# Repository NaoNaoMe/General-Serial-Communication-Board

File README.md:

General Serial Communication Board
=========

The General Serial Communication Board is an USB to Serial converter with FTDI Chipset.  
Full/Half-duplex UART, DTR/RTS signals, and 3-position will be adapted microcontroller you may use.  
These features are useful for serial flash programming.  
This board also has opto-isolaters to prevent electrical shock, get rid of Ground Loop track and protect your computer.  

### Some highlights of the General Serial Communication Board:
 1. USB UART Bridge: FTDI FT231X Based on the popular FTDI FT231X converter
 2. UART interface circuit accepts 3.3V and 5.0V.
 3. Electrical isolation between UART interface and USB interface.
 4. All standard serial data rates and up to 3Mega baud.
 5. Full duplex mode and Half duplex mode are selectable(SW4).
 6. Flow control pins are avilable (DTR or RTS, SW1) and (DSR or CTS, SW2)
 7. 3-state user switch(SW3) connected to ftdi is selectable VCC, weak pulldown or GND.
 8. Measures 40mm x 80mm x 20mm

Repository Contents
-------------------
* **/Mechanical** - Mechanical data files (.dxf, .dwg)
* **/Hardware** - All Eagle design files (.brd, .sch)

Description(Pin Interfaces)
-------------------

### CN1(Primarily) Connector Descriptions:
Micro B-type usb connector

### CN2(Secondary) Connector Descriptions:
Barrel Power Jack socket
This socket is connected to VIN pin on CN3 with the main power switch(SW5).  
The power supply must follow microcontroller requirements.

### CN3(Secondary) Pin Descriptions:
This connector is for your target boart.
- **VIN:** UART interface power supply with a voltage range of 2.7 to 5.5VDC.
- **TX:** Full duplex TX signal(CMOS TTL output).
- **TX/RX:** Half duplex signals(Open collector output).
- **RX:** Full duplex RX signal.
- **GND:** GND.
- **I/S:** User switch (Active High signal) and input to DSR or CTS.
- **OUT:** DTR or RTS signal (Active High signal).

License Information
-------------------
The repository is released under [Creative Commons ShareAlike 4.0 International](https://creativecommons.org/licenses/by-sa/4.0/).

Distributed as-is; no warranty is given.

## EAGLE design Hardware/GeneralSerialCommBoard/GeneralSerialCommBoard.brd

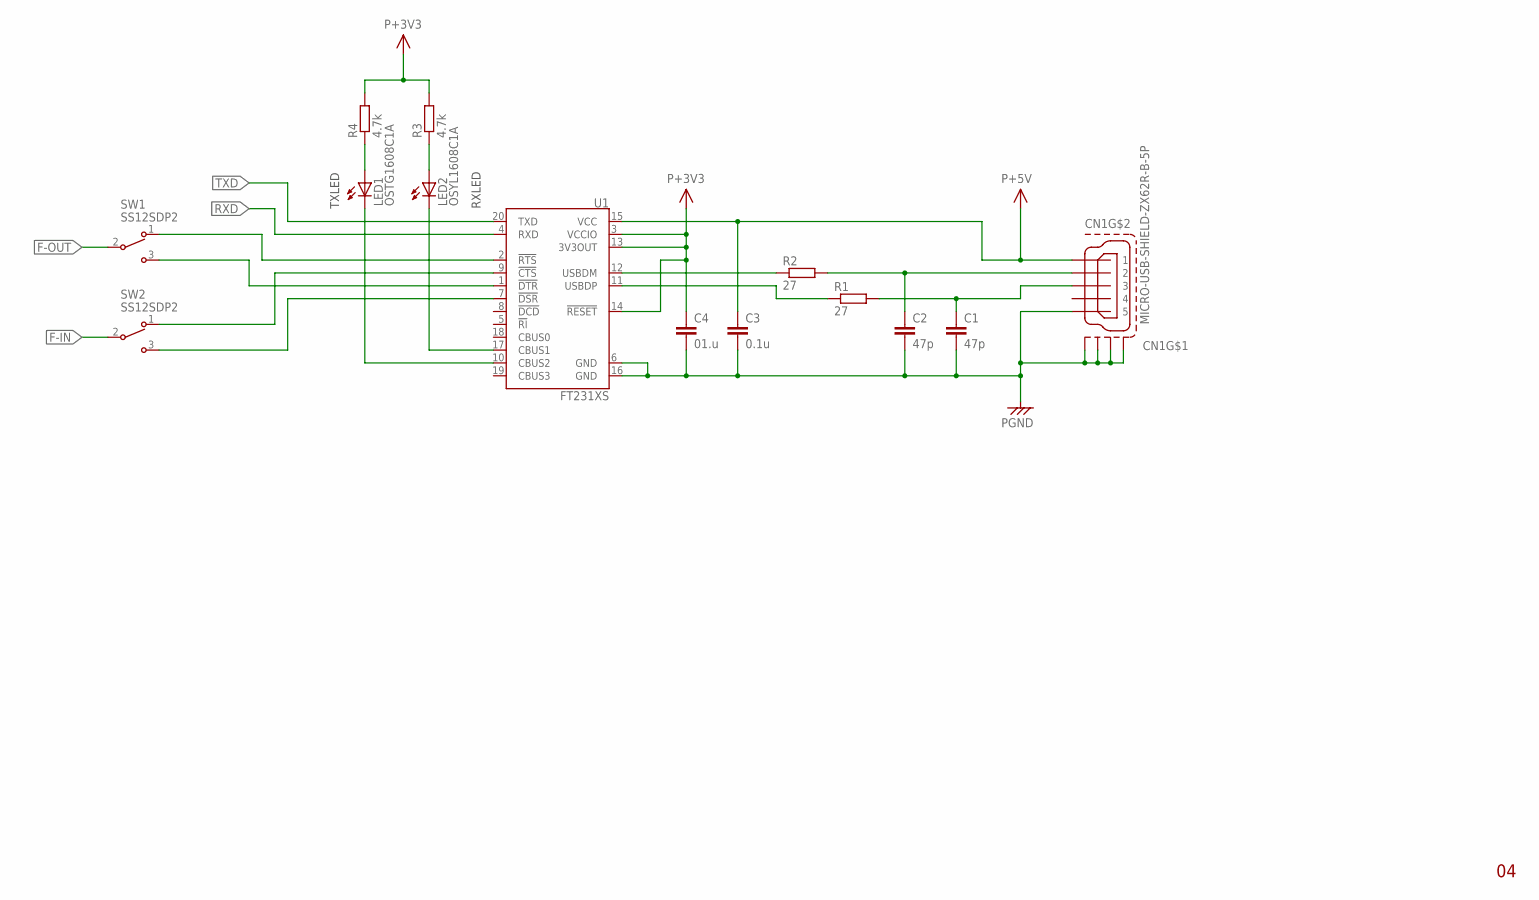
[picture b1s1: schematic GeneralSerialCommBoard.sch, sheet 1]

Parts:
C1, C2: 47p; C0603
C3: 0.1u; C0603
C4: 01.u; C0603
CN1: MICRO-USB-SHIELD-ZX62R-B-5P; ZX62R-B-5P
LED1: OSTG1608C1A; 1608SMD
LED2: OSYL1608C1A; 1608SMD
R1, R2: 27; R0603
R3, R4: 4.7k; R0603
SW1, SW2: SS12SDP2
U1: FT231XS; SSOP20_L

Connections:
CBUS1: LED2.K (C), U1.17 (CBUS1)
CBUS2: LED1.K (C), U1.10 (CBUS2)
CTS: SW2.1 (T1), U1.9 (!CTS)
DSR: SW2.3 (T3), U1.7 (!DSR)
DTR: SW1.3 (T3), U1.1 (!DTR)
F-IN: SW2.2 (COM2); also elsewhere on the board
F-OUT: SW1.2 (COM2); also elsewhere on the board
unnamed: C1.1, CN1.3, R1.2
unnamed: C2.1, CN1.2, R2.2
unnamed: LED2.A, R3.1
unnamed: LED1.A, R4.1
unnamed: R2.1, U1.12 (USBDM)
unnamed: R1.1, U1.11 (USBDP)
P+3V3: C4.1, R3.2, R4.2, U1.3 (VCCIO), U1.13 (3V3OUT), U1.14 (!RESET); also elsewhere on the board
P+5V: C3.1, CN1.1, U1.15 (VCC)
PGND: C1.2, C2.2, C3.2, C4.2, CN1.5, CN1.M1 (S1), CN1.M2 (S2), CN1.M3 (S3), CN1.M4 (S4), U1.6 (GND), U1.16 (GND); also elsewhere on the board
RTS: SW1.1 (T1), U1.2 (!RTS)
RXD: U1.4 (RXD); also elsewhere on the board
TXD: U1.20 (TXD); also elsewhere on the board

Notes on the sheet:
TXLED
RXLED

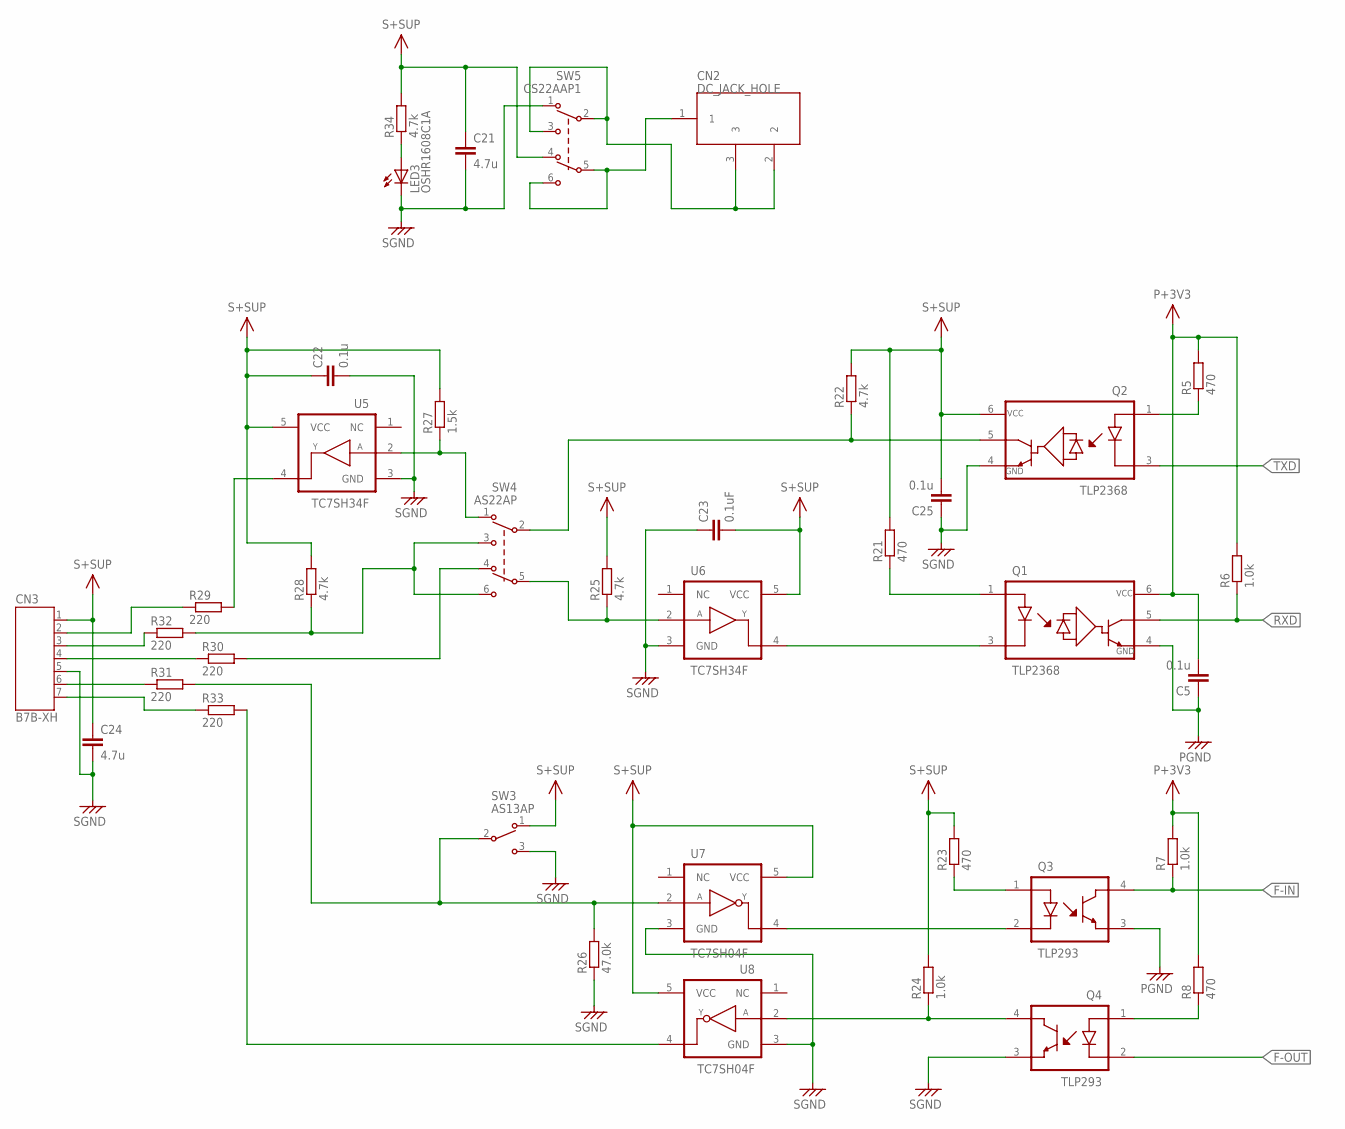
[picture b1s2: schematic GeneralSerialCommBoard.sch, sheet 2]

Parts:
C5, C22, C25: 0.1u; C0603
C21, C24: 4.7u; C1206
C23: 0.1uF; C0603
CN2: DC_JACK_HOLE
CN3: B7B-XH
LED3: OSHR1608C1A; 1608SMD
Q1, Q2: TLP2368; SO6-5PIN
Q3, Q4: TLP293; SO4
R5, R8, R21, R23: 470; R0603
R6, R7, R24: 1.0k; R0603
R22, R25, R28, R34: 4.7k; R0603
R26: 47.0k; R0603
R27: 1.5k; R0603
R29, R30, R31, R32, R33: 220; R0603
SW3: AS13AP
SW4: AS22AP
SW5: CS22AAP1
U5, U6: TC7SH34F; SMV
U7, U8: TC7SH04F; SMV

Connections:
F-IN: Q3.4 (C), R7.1; also elsewhere on the board
F-OUT: Q4.2 (K); also elsewhere on the board
unnamed: CN2.1, SW5.5 (COM5), SW5.6 (T6)
unnamed: CN2.2, CN2.3, SW5.2 (COM2), SW5.3 (T3)
unnamed: Q2.1 (A), R5.1
unnamed: Q2.5 (VO), R22.1, SW4.2 (COM2)
unnamed: Q4.1 (A), R8.1
unnamed: CN3.2, R29.1
unnamed: CN3.3, R32.1
unnamed: CN3.4, R30.1
unnamed: CN3.6, R31.1
unnamed: CN3.7, R33.1
unnamed: R29.2, U5.4 (Y)
unnamed: R28.1, R32.2, SW4.3 (T3), SW4.6 (T6)
unnamed: R27.1, SW4.1 (T1), U5.2 (A)
unnamed: Q1.1 (A), R21.1
unnamed: R30.2, SW4.4 (T4)
unnamed: R25.1, SW4.5 (COM5), U6.2 (A)
unnamed: Q1.3 (K), U6.4 (Y)
unnamed: Q3.1 (A), R23.1
unnamed: Q3.2 (K), U7.4 (Y)
unnamed: Q4.4 (C), R24.1, U8.2 (A)
unnamed: R26.2, R31.2, SW3.2 (COM2), U7.2 (A)
unnamed: R33.2, U8.4 (Y)
unnamed: LED3.A, R34.1
P+3V3: C5.2, Q1.6 (VCC), R5.2, R6.2, R7.2, R8.2; also elsewhere on the board
PGND: C5.1, Q1.4 (GND), Q3.3 (E); also elsewhere on the board
RXD: Q1.5 (VO), R6.1; also elsewhere on the board
S+SUP: C21.1, C22.1, C23.2, C24.1, C25.2, CN3.1, Q2.6 (VCC), R21.2, R22.2, R23.2, R24.2, R25.2, R27.2, R28.2, R34.2, SW3.1 (T1), SW5.4 (T4), U5.5 (VCC), U6.5 (VCC), U7.5 (VCC), U8.5 (VCC)
SGND: C21.2, C22.2, C23.1, C24.2, C25.1, CN3.5, LED3.K (C), Q2.4 (GND), Q4.3 (E), R26.1, SW3.3 (T3), SW5.1 (T1), U5.3 (GND), U6.3 (GND), U7.3 (GND), U8.3 (GND)
TXD: Q2.3 (K); also elsewhere on the board

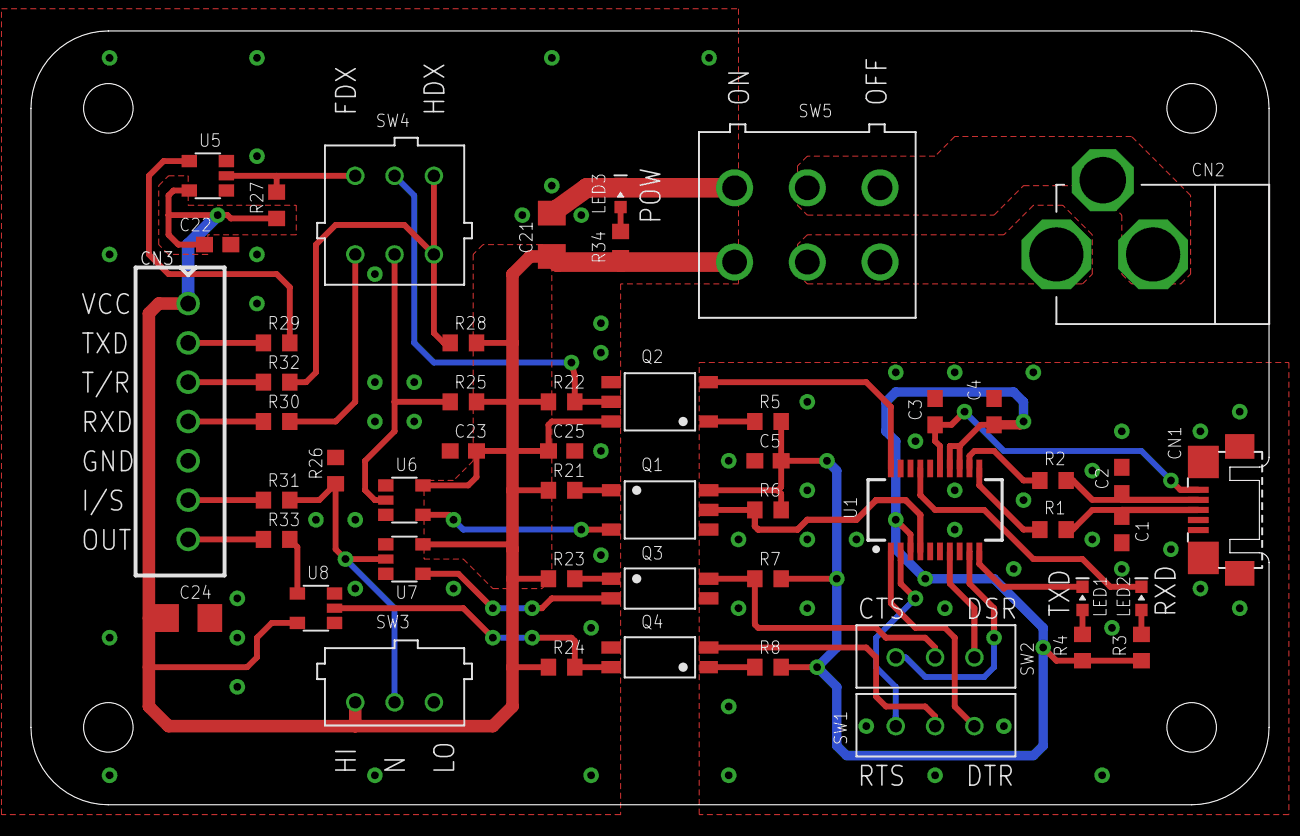
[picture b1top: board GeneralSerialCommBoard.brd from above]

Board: 2 copper layers, 80.0 x 50.0 mm, 52 parts (0 on the bottom side), 44 nets.

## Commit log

2017-03-31 add files

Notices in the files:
parts and their libraries:
jst: Copyright (C) 2016, Naoya Imai
ftdi: Copyright (C) sparkfun
